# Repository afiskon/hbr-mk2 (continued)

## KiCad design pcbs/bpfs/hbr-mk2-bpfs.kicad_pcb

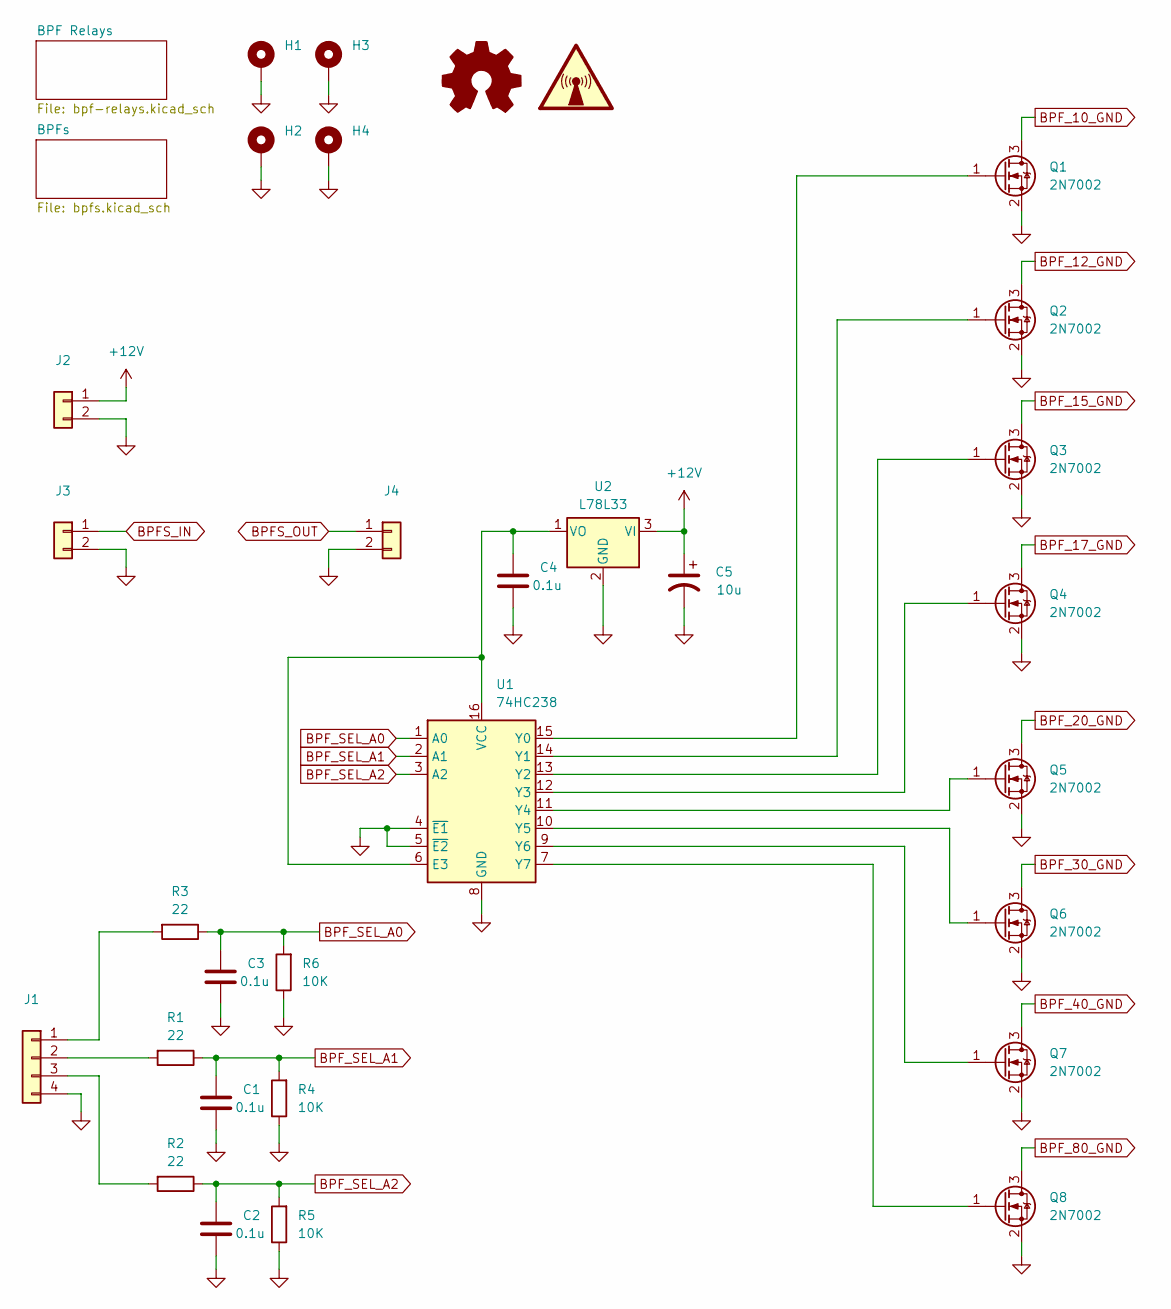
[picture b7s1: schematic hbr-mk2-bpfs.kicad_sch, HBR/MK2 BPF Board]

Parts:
C1, C2, C3, C4: 0.1u; C_0805_2012Metric_Pad1.18x1.45mm_HandSolder
C5: 10u; CP_Elec_4x5.4
H1, H2, H3, H4: MountingHole_Pad; MountingHole_3.5mm_Pad_Via
J1: Conn_01x04; PinHeader_1x04_P2.54mm_Vertical
J2, J3, J4: Conn_01x02; PinHeader_1x02_P2.54mm_Vertical
Q1, Q2, Q3, Q4, Q5, Q6, Q7, Q8: 2N7002; SOT-23
R1, R2, R3: 22; R_0805_2012Metric_Pad1.20x1.40mm_HandSolder
R4, R5, R6: 10K; R_0805_2012Metric_Pad1.20x1.40mm_HandSolder
SYM1: Logo_Open_Hardware_Small; OSHW-Logo2_9.8x8mm_SilkScreen
SYM2: SYM_Radio_Waves_Large; KiCad-Logo2_5mm_SilkScreen
U1: 74HC238; SO-16_5.3x10.2mm_P1.27mm
U2: L78L33; TO-92_HandSolder

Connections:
+12V: C5.1, J2.1, U2.3 (VI); also elsewhere on the board
BPFS_IN: J3.1; also elsewhere on the board
BPFS_OUT: J4.1; also elsewhere on the board
BPF_10_GND: Q1.3 (D); also elsewhere on the board
BPF_12_GND: Q2.3 (D); also elsewhere on the board
BPF_15_GND: Q3.3 (D); also elsewhere on the board
BPF_17_GND: Q4.3 (D); also elsewhere on the board
BPF_20_GND: Q5.3 (D); also elsewhere on the board
BPF_30_GND: Q6.3 (D); also elsewhere on the board
BPF_40_GND: Q7.3 (D); also elsewhere on the board
BPF_80_GND: Q8.3 (D); also elsewhere on the board
BPF_SEL_A0: C3.2, R3.1, R6.2, U1.1 (A0)
BPF_SEL_A1: C1.2, R1.1, R4.2, U1.2 (A1)
BPF_SEL_A2: C2.2, R2.1, R5.2, U1.3 (A2)
GND: C1.1, C2.1, C3.1, C4.1, C5.2, H1.1, H2.1, H3.1, H4.1, J1.4, J2.2, J3.2, J4.2, Q1.2 (S), Q2.2 (S), Q3.2 (S), Q4.2 (S), Q5.2 (S), Q6.2 (S), Q7.2 (S), Q8.2 (S), R4.1, R5.1, R6.1, U1.4 (~E1), U1.5 (~E2), U1.8 (GND), U2.2 (GND); also elsewhere on the board
unnamed: J1.1, R3.2
unnamed: J1.2, R1.2
unnamed: J1.3, R2.2
unnamed: Q1.1 (G), U1.15 (Y0)
unnamed: Q2.1 (G), U1.14 (Y1)
unnamed: Q3.1 (G), U1.13 (Y2)
unnamed: Q4.1 (G), U1.12 (Y3)
unnamed: Q5.1 (G), U1.11 (Y4)
unnamed: Q6.1 (G), U1.10 (Y5)
unnamed: Q7.1 (G), U1.9 (Y6)
unnamed: Q8.1 (G), U1.7 (Y7)
unnamed: C4.2, U1.6 (E3), U1.16 (VCC), U2.1 (VO)

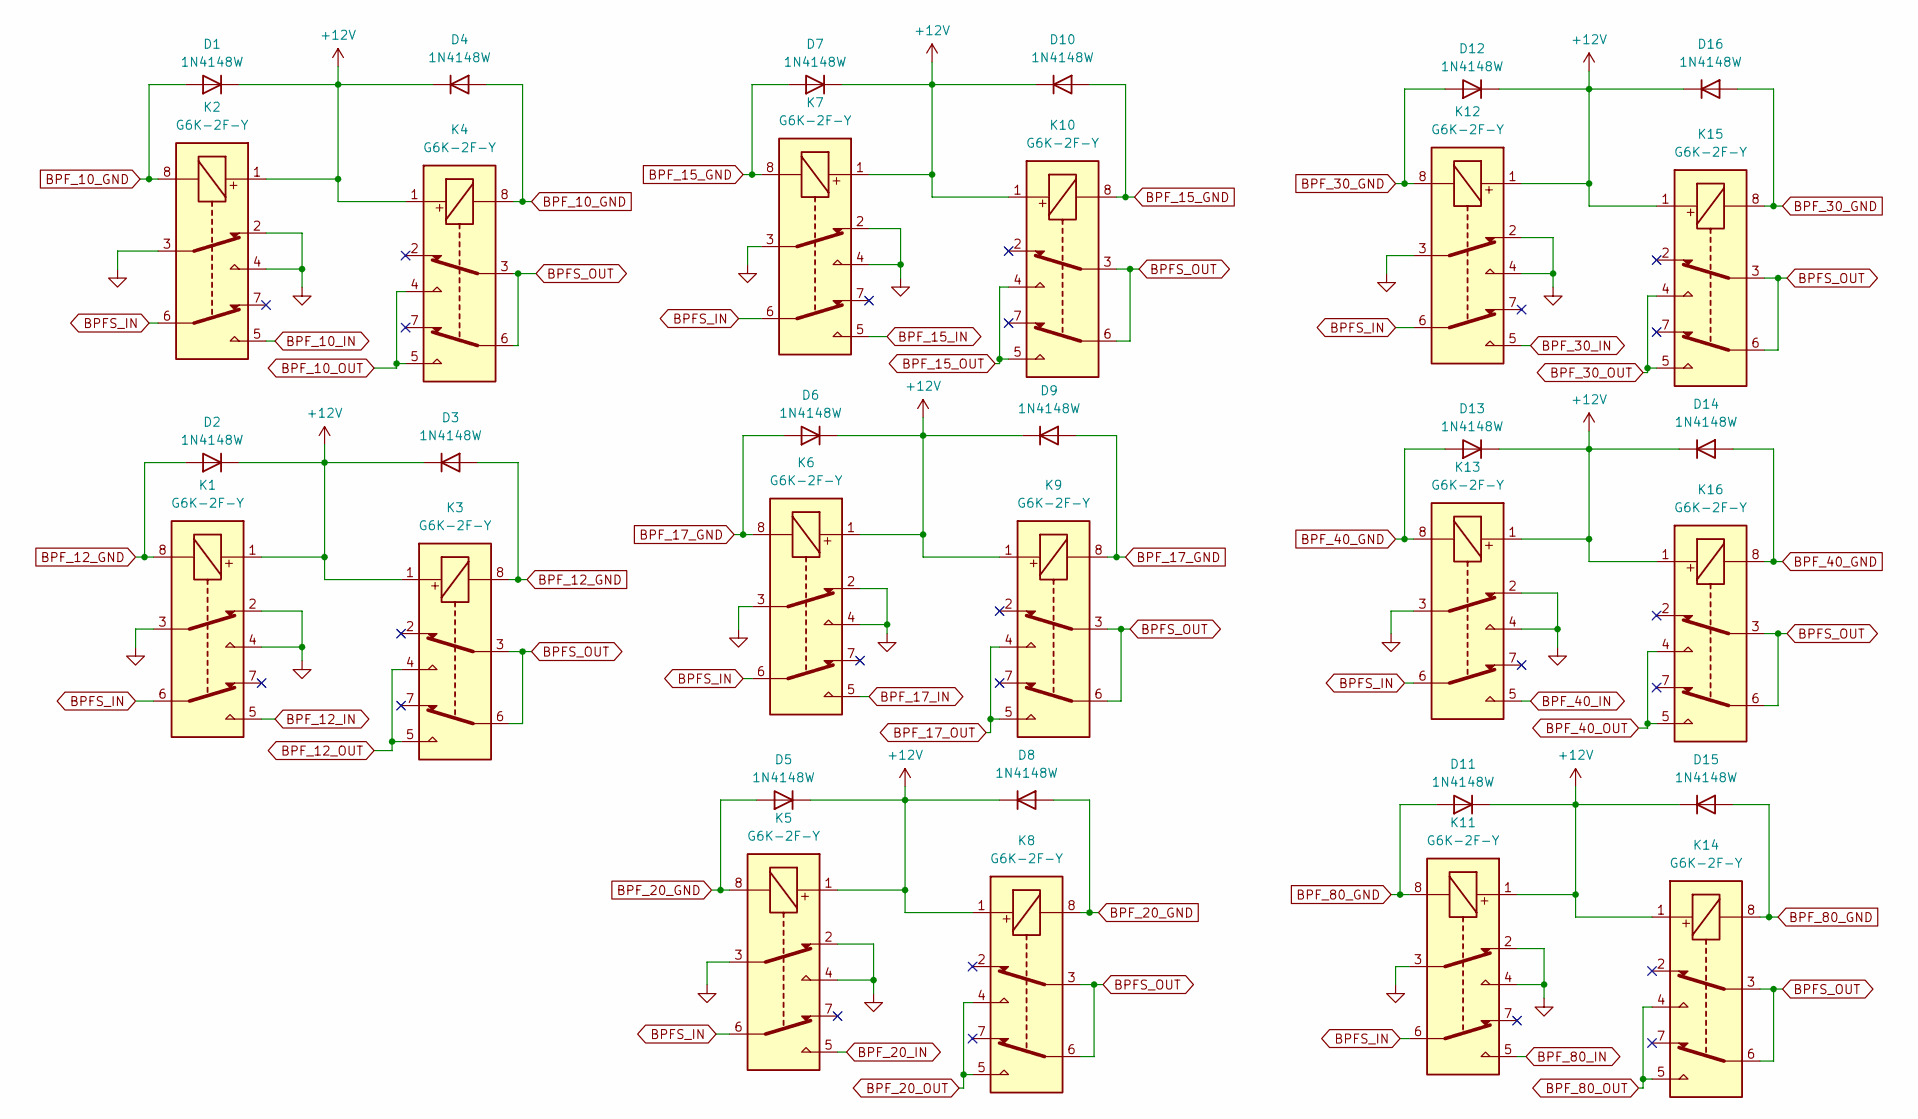
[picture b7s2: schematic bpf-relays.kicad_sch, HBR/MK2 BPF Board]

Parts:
D1, D2, D3, D4, D5, D6, D7, D8, D9, D10, D11, D12, D13, D14, D15, D16: 1N4148W; D_SOD-123
K1, K2, K3, K4, K5, K6, K7, K8, K9, K10, K11, K12, K13, K14, K15, K16: G6K-2F-Y; Relay_DPDT_Omron_G6K-2F-Y

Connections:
+12V: D1.1 (K), D2.1 (K), D3.1 (K), D4.1 (K), D5.1 (K), D6.1 (K), D7.1 (K), D8.1 (K), D9.1 (K), D10.1 (K), D11.1 (K), D12.1 (K), D13.1 (K), D14.1 (K), D15.1 (K), D16.1 (K), K1.1, K2.1, K3.1, K4.1, K5.1, K6.1, K7.1, K8.1, K9.1, K10.1, K11.1, K12.1, K13.1, K14.1, K15.1, K16.1; also elsewhere on the board
BPFS_IN: K1.6, K2.6, K5.6, K6.6, K7.6, K11.6, K12.6, K13.6; also elsewhere on the board
BPFS_OUT: K3.3, K3.6, K4.3, K4.6, K8.3, K8.6, K9.3, K9.6, K10.3, K10.6, K14.3, K14.6, K15.3, K15.6, K16.3, K16.6; also elsewhere on the board
BPF_10_GND: D1.2 (A), D4.2 (A), K2.8, K4.8; also elsewhere on the board
BPF_10_IN: K2.5; also elsewhere on the board
BPF_10_OUT: K4.4, K4.5; also elsewhere on the board
BPF_12_GND: D2.2 (A), D3.2 (A), K1.8, K3.8; also elsewhere on the board
BPF_12_IN: K1.5; also elsewhere on the board
BPF_12_OUT: K3.4, K3.5; also elsewhere on the board
BPF_15_GND: D7.2 (A), D10.2 (A), K7.8, K10.8; also elsewhere on the board
BPF_15_IN: K7.5; also elsewhere on the board
BPF_15_OUT: K10.4, K10.5; also elsewhere on the board
BPF_17_GND: D6.2 (A), D9.2 (A), K6.8, K9.8; also elsewhere on the board
BPF_17_IN: K6.5; also elsewhere on the board
BPF_17_OUT: K9.4, K9.5; also elsewhere on the board
BPF_20_GND: D5.2 (A), D8.2 (A), K5.8, K8.8; also elsewhere on the board
BPF_20_IN: K5.5; also elsewhere on the board
BPF_20_OUT: K8.4, K8.5; also elsewhere on the board
BPF_30_GND: D12.2 (A), D16.2 (A), K12.8, K15.8; also elsewhere on the board
BPF_30_IN: K12.5; also elsewhere on the board
BPF_30_OUT: K15.4, K15.5; also elsewhere on the board
BPF_40_GND: D13.2 (A), D14.2 (A), K13.8, K16.8; also elsewhere on the board
BPF_40_IN: K13.5; also elsewhere on the board
BPF_40_OUT: K16.4, K16.5; also elsewhere on the board
BPF_80_GND: D11.2 (A), D15.2 (A), K11.8, K14.8; also elsewhere on the board
BPF_80_IN: K11.5; also elsewhere on the board
BPF_80_OUT: K14.4, K14.5; also elsewhere on the board
GND: K1.2, K1.3, K1.4, K2.2, K2.3, K2.4, K5.2, K5.3, K5.4, K6.2, K6.3, K6.4, K7.2, K7.3, K7.4, K11.2, K11.3, K11.4, K12.2, K12.3, K12.4, K13.2, K13.3, K13.4; also elsewhere on the board

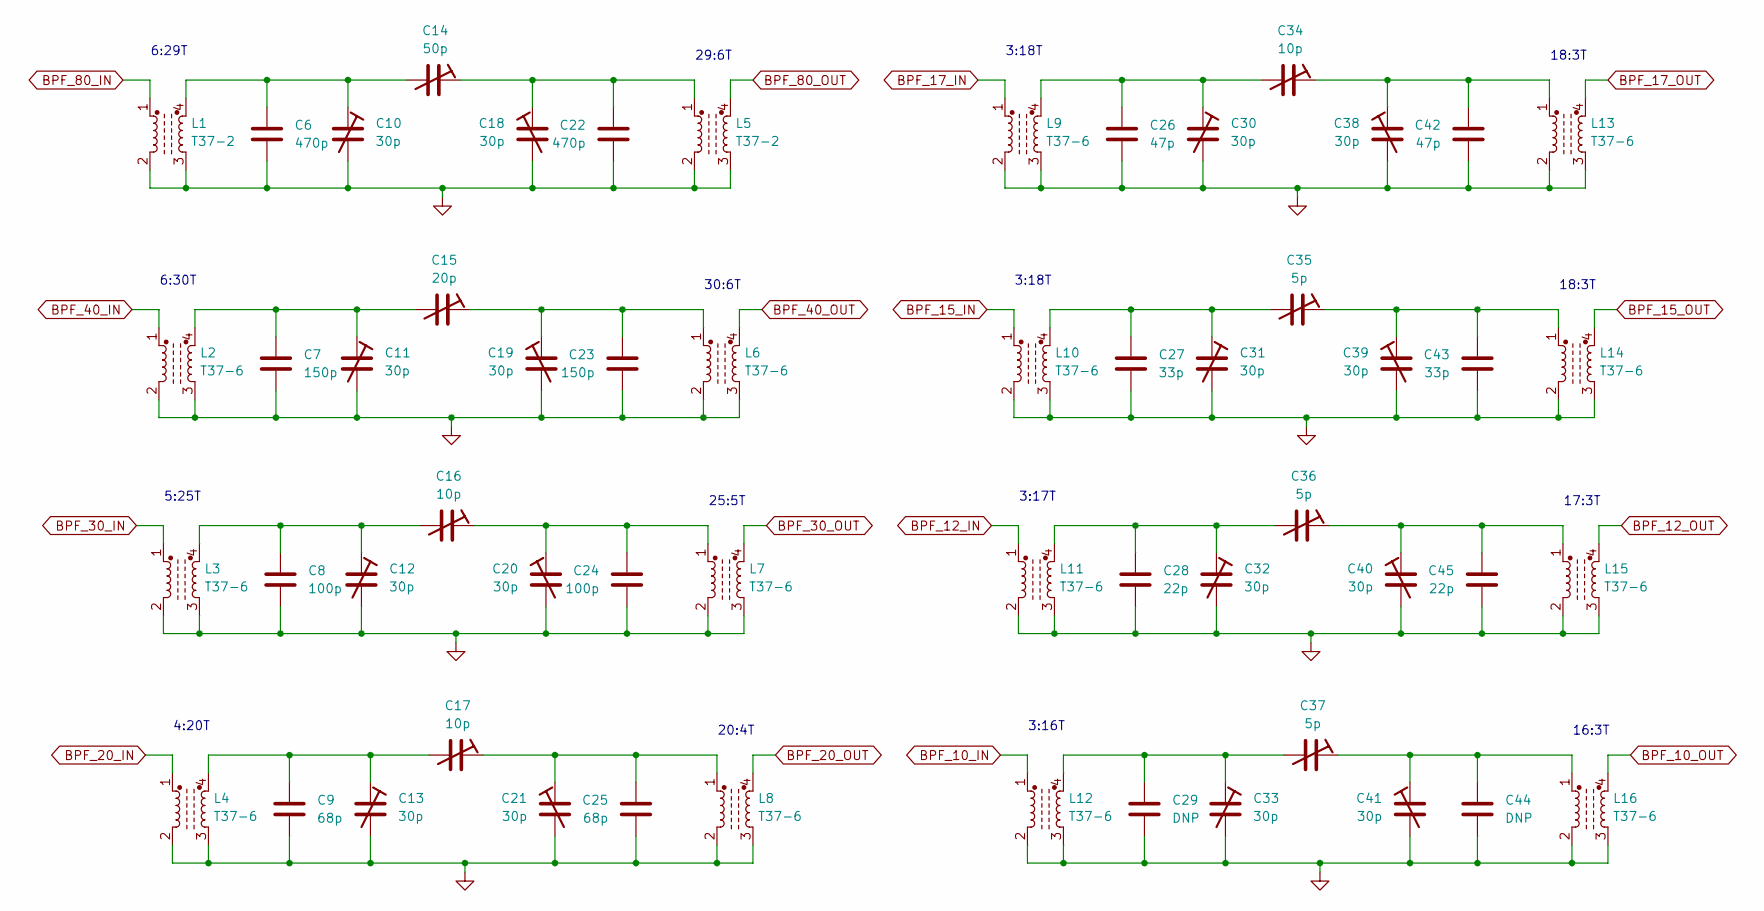
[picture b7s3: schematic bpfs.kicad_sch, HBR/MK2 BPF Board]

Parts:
C6, C22: 470p; C_0805_2012Metric_Pad1.18x1.45mm_HandSolder
C7, C23: 150p; C_0805_2012Metric_Pad1.18x1.45mm_HandSolder
C8, C24: 100p; C_0805_2012Metric_Pad1.18x1.45mm_HandSolder
C9, C25: 68p; C_0805_2012Metric_Pad1.18x1.45mm_HandSolder
C10, C11, C12, C13, C18, C19, C20, C21, C30, C31, C32, C33, C38, C39, C40, C41: 30p; C_Trim_THD_L7.0mm_W6.5mm_P5.00mm
C14: 50p; C_Trim_THD_L7.0mm_W6.5mm_P5.00mm
C15: 20p; C_Trim_THD_L7.0mm_W6.5mm_P5.00mm
C16, C17, C34: 10p; C_Trim_THD_L7.0mm_W6.5mm_P5.00mm
C26, C42: 47p; C_0805_2012Metric_Pad1.18x1.45mm_HandSolder
C27, C43: 33p; C_0805_2012Metric_Pad1.18x1.45mm_HandSolder
C28, C45: 22p; C_0805_2012Metric_Pad1.18x1.45mm_HandSolder
C29, C44: DNP; C_0805_2012Metric_Pad1.18x1.45mm_HandSolder
C35, C36, C37: 5p; C_Trim_THD_L7.0mm_W6.5mm_P5.00mm
L1, L5: T37-2; DIP-4_W7.62mm
L2, L3, L4, L6, L7, L8, L9, L10, L11, L12, L13, L14, L15, L16: T37-6; DIP-4_W7.62mm

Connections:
BPF_10_IN: L12.1; also elsewhere on the board
BPF_10_OUT: L16.4; also elsewhere on the board
BPF_12_IN: L11.1; also elsewhere on the board
BPF_12_OUT: L15.4; also elsewhere on the board
BPF_15_IN: L10.1; also elsewhere on the board
BPF_15_OUT: L14.4; also elsewhere on the board
BPF_17_IN: L9.1; also elsewhere on the board
BPF_17_OUT: L13.4; also elsewhere on the board
BPF_20_IN: L4.1; also elsewhere on the board
BPF_20_OUT: L8.4; also elsewhere on the board
BPF_30_IN: L3.1; also elsewhere on the board
BPF_30_OUT: L7.4; also elsewhere on the board
BPF_40_IN: L2.1; also elsewhere on the board
BPF_40_OUT: L6.4; also elsewhere on the board
BPF_80_IN: L1.1; also elsewhere on the board
BPF_80_OUT: L5.4; also elsewhere on the board
GND: C6.2, C7.2, C8.2, C9.2, C10.2, C11.2, C12.2, C13.2, C18.2, C19.2, C20.2, C21.2, C22.2, C23.2, C24.2, C25.2, C26.2, C27.2, C28.2, C29.2, C30.2, C31.2, C32.2, C33.2, C38.2, C39.2, C40.2, C41.2, C42.2, C43.2, C44.2, C45.2, L1.2, L1.3, L2.2, L2.3, L3.2, L3.3, L4.2, L4.3, L5.2, L5.3, L6.2, L6.3, L7.2, L7.3, L8.2, L8.3, L9.2, L9.3, L10.2, L10.3, L11.2, L11.3, L12.2, L12.3, L13.2, L13.3, L14.2, L14.3, L15.2, L15.3, L16.2, L16.3; also elsewhere on the board
unnamed: C6.1, C10.1, C14.2, L1.4
unnamed: C7.1, C11.1, C15.2, L2.4
unnamed: C8.1, C12.1, C16.2, L3.4
unnamed: C9.1, C13.1, C17.2, L4.4
unnamed: C14.1, C18.1, C22.1, L5.1
unnamed: C15.1, C19.1, C23.1, L6.1
unnamed: C16.1, C20.1, C24.1, L7.1
unnamed: C17.1, C21.1, C25.1, L8.1
unnamed: C26.1, C30.1, C34.2, L9.4
unnamed: C27.1, C31.1, C35.2, L10.4
unnamed: C28.1, C32.1, C36.2, L11.4
unnamed: C29.1, C33.1, C37.2, L12.4
unnamed: C34.1, C38.1, C42.1, L13.1
unnamed: C35.1, C39.1, C43.1, L14.1
unnamed: C36.1, C40.1, C45.1, L15.1
unnamed: C37.1, C41.1, C44.1, L16.1

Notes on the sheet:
18:3T
3:18T
6:29T
5:25T
3:16T
4:20T
29:6T
16:3T
20:4T
6:30T
30:6T
17:3T
3:17T
25:5T

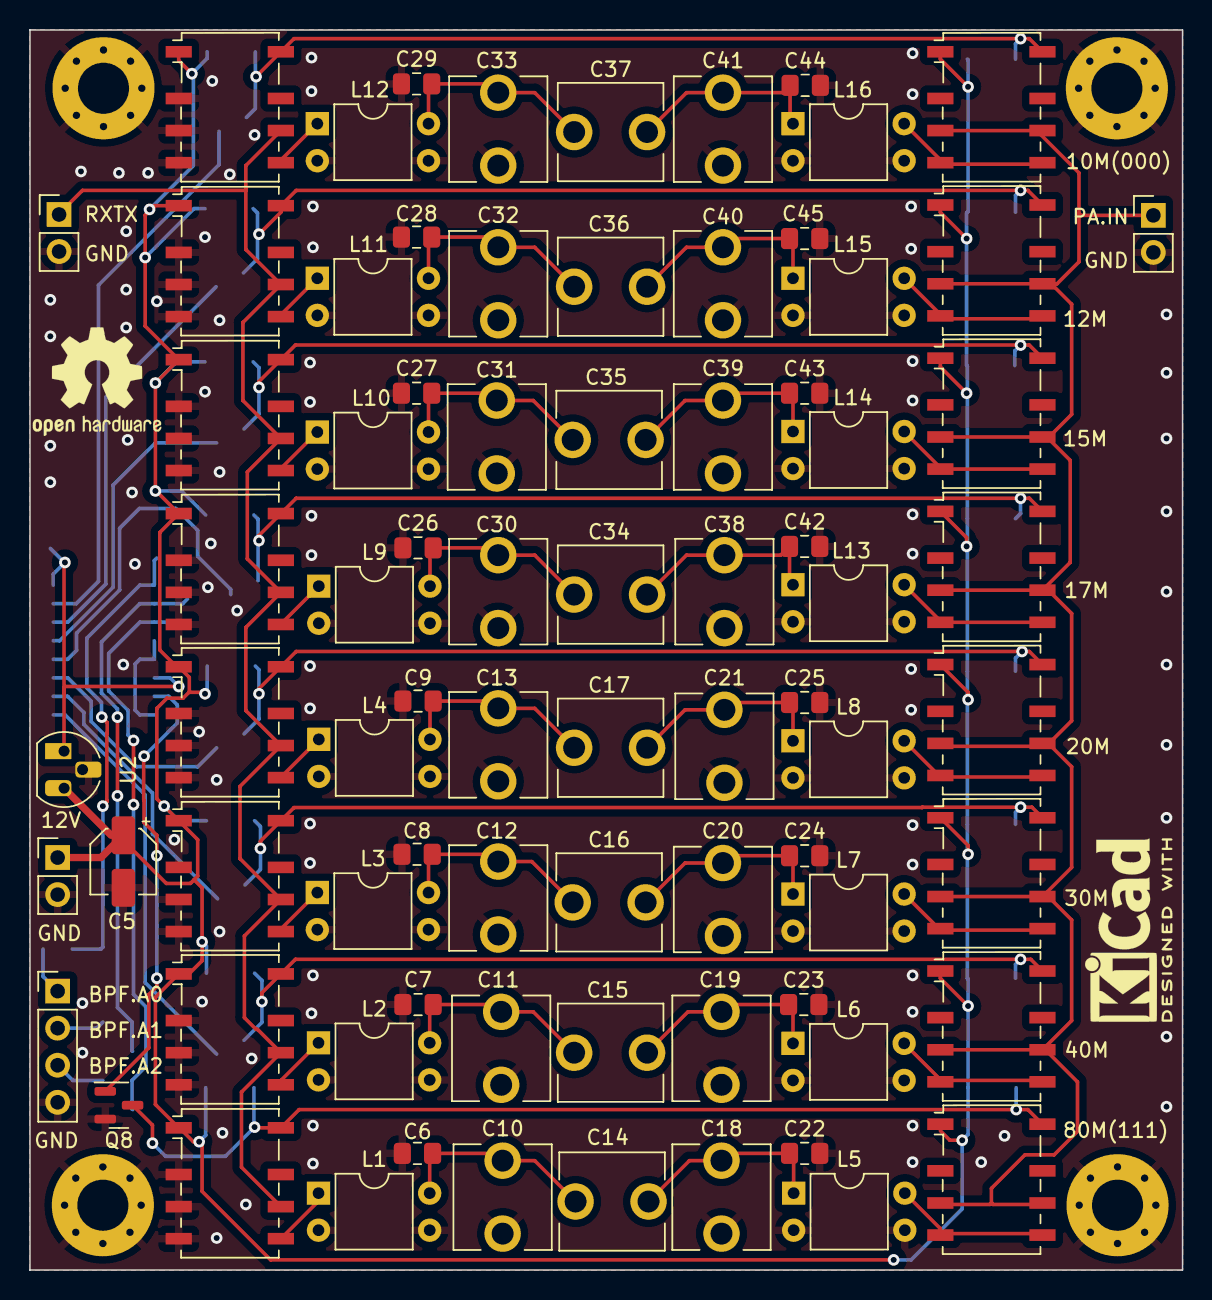
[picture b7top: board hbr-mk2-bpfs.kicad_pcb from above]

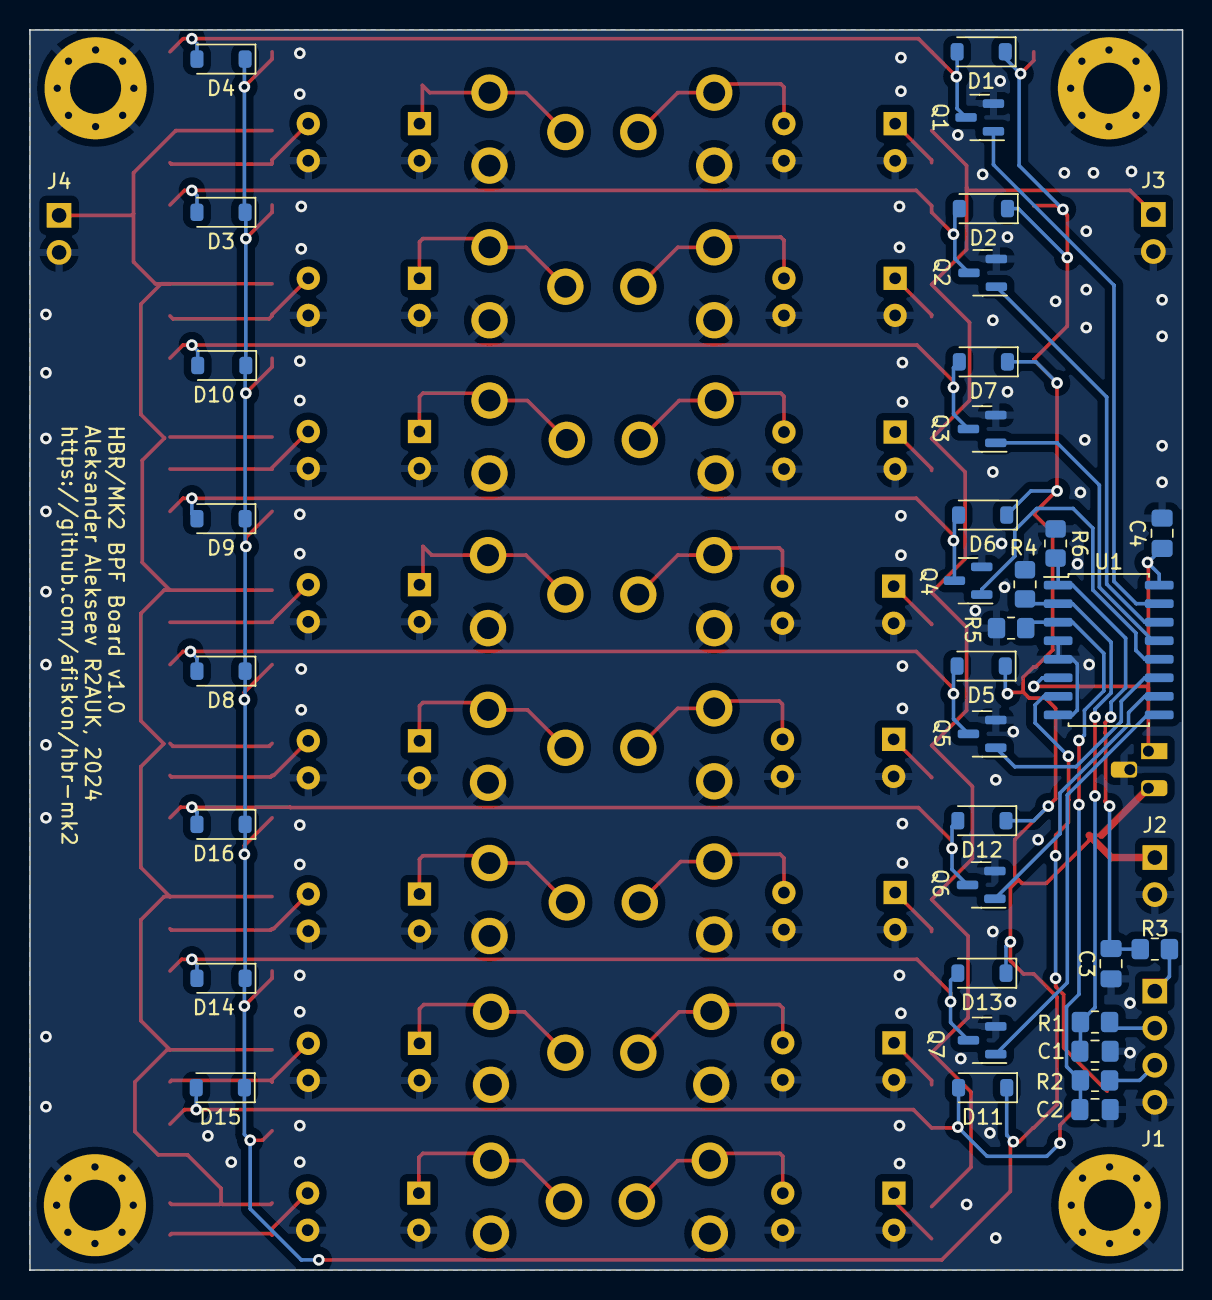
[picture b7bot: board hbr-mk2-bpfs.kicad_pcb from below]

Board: 2 copper layers, 79.0 x 85.0 mm, 119 parts (34 on the bottom side), 59 nets.

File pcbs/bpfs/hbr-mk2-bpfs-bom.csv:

Reference(s),Qty,Value,Footprint
"C1, C2, C3, C4",4,0.1u,Capacitor_SMD:C_0805_2012Metric_Pad1.18x1.45mm_HandSolder
C5,1,10u,Capacitor_SMD:CP_Elec_4x5.4
"C6, C22",2,470p,Capacitor_SMD:C_0805_2012Metric_Pad1.18x1.45mm_HandSolder
"C7, C23",2,150p,Capacitor_SMD:C_0805_2012Metric_Pad1.18x1.45mm_HandSolder
"C8, C24",2,100p,Capacitor_SMD:C_0805_2012Metric_Pad1.18x1.45mm_HandSolder
"C9, C25",2,68p,Capacitor_SMD:C_0805_2012Metric_Pad1.18x1.45mm_HandSolder
"C10, C11, C12, C13, C18, C19, C20, C21, C30, C31, C32, C33, C38, C39, C40, C41",16,30p,My_Library:C_Trim_THD_L7.0mm_W6.5mm_P5.00mm
C14,1,50p,My_Library:C_Trim_THD_L7.0mm_W6.5mm_P5.00mm
C15,1,20p,My_Library:C_Trim_THD_L7.0mm_W6.5mm_P5.00mm
"C16, C17, C34",3,10p,My_Library:C_Trim_THD_L7.0mm_W6.5mm_P5.00mm
"C26, C42",2,47p,Capacitor_SMD:C_0805_2012Metric_Pad1.18x1.45mm_HandSolder
"C27, C43",2,33p,Capacitor_SMD:C_0805_2012Metric_Pad1.18x1.45mm_HandSolder
"C28, C45",2,22p,Capacitor_SMD:C_0805_2012Metric_Pad1.18x1.45mm_HandSolder
"C35, C36, C37",3,5p,My_Library:C_Trim_THD_L7.0mm_W6.5mm_P5.00mm
"D1, D2, D3, D4, D5, D6, D7, D8, D9, D10, D11, D12, D13, D14, D15, D16",16,1N4148W,Diode_SMD:D_SOD-123
"K1, K2, K3, K4, K5, K6, K7, K8, K9, K10, K11, K12, K13, K14, K15, K16",16,G6K-2F-Y,Relay_SMD:Relay_DPDT_Omron_G6K-2F-Y
"L1, L5",2,T37-2,Package_DIP:DIP-4_W7.62mm
"L2, L3, L4, L6, L7, L8, L9, L10, L11, L12, L13, L14, L15, L16",14,T37-6,Package_DIP:DIP-4_W7.62mm
"Q1, Q2, Q3, Q4, Q5, Q6, Q7, Q8",8,2N7002,Package_TO_SOT_SMD:SOT-23
"R1, R2, R3",3,22,Resistor_SMD:R_0805_2012Metric_Pad1.20x1.40mm_HandSolder
"R4, R5, R6",3,10K,Resistor_SMD:R_0805_2012Metric_Pad1.20x1.40mm_HandSolder
U1,1,74HC238,Package_SO:SO-16_5.3x10.2mm_P1.27mm
U2,1,L78L33,Package_TO_SOT_THT:TO-92_HandSolder

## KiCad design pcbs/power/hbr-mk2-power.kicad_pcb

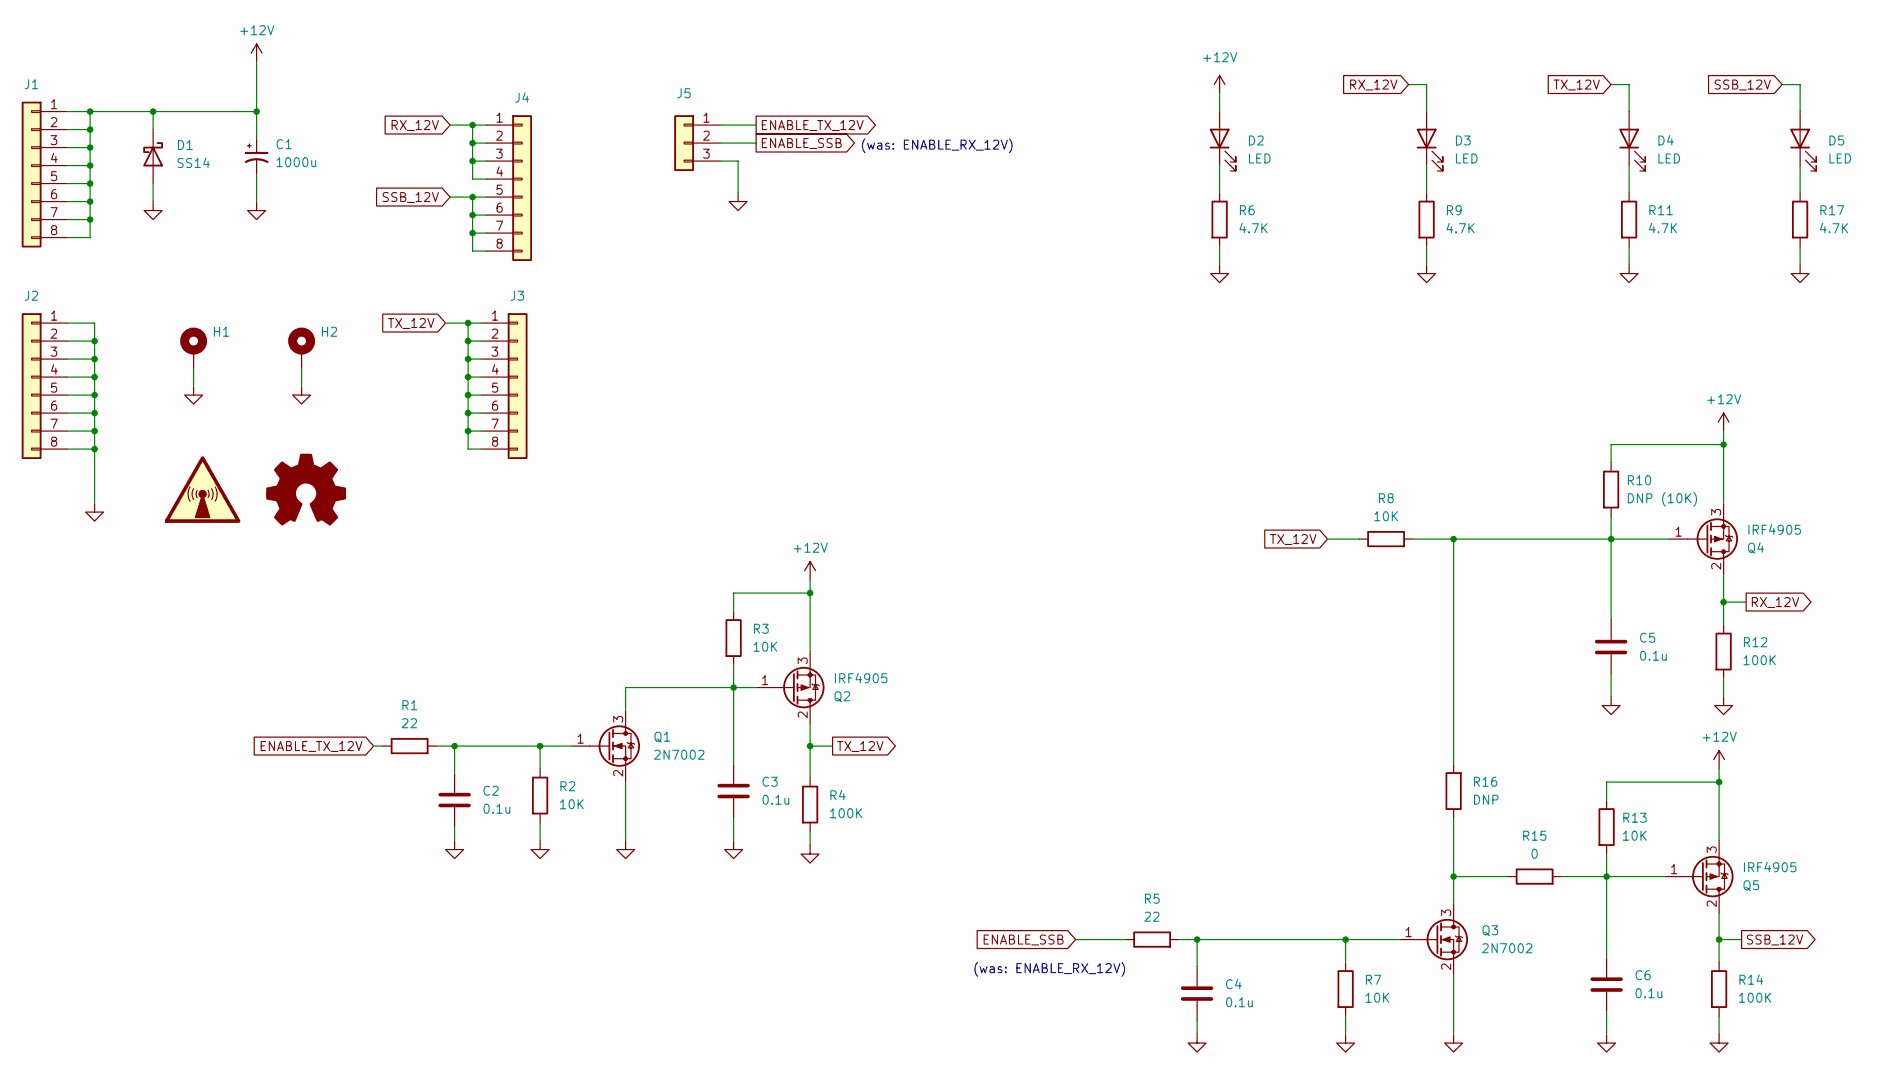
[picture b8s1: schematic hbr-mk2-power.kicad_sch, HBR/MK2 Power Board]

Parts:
C1: 1000u; CP_Radial_D13.0mm_P5.00mm
C2, C3, C4, C5, C6: 0.1u; C_0805_2012Metric_Pad1.18x1.45mm_HandSolder
D1: SS14; D_SMA_Handsoldering
D2, D3, D4, D5: LED; LED_0805_2012Metric_Pad1.15x1.40mm_HandSolder
H1, H2: MountingHole_Pad; MountingHole_3.5mm_Pad_Via
J1, J2, J3, J4: Conn_01x08; PinHeader_1x08_P2.54mm_Vertical
J5: Conn_01x03; PinSocket_1x03_P2.54mm_Vertical
Q1, Q3: 2N7002; SOT-23
Q2, Q4, Q5: IRF4905; TO-220-3_Vertical
R1, R5: 22; R_0805_2012Metric_Pad1.20x1.40mm_HandSolder
R2, R3, R7, R8, R13: 10K; R_0805_2012Metric_Pad1.20x1.40mm_HandSolder
R4, R12, R14: 100K; R_0805_2012Metric_Pad1.20x1.40mm_HandSolder
R6, R9, R11, R17: 4.7K; R_0805_2012Metric_Pad1.20x1.40mm_HandSolder
R10: DNP (10K); R_0805_2012Metric_Pad1.20x1.40mm_HandSolder
R15: 0; R_0805_2012Metric_Pad1.20x1.40mm_HandSolder
R16: DNP; R_0805_2012Metric_Pad1.20x1.40mm_HandSolder
SYM1: SYM_Radio_Waves_Large; KiCad-Logo2_5mm_SilkScreen
SYM2: Logo_Open_Hardware_Small; OSHW-Logo2_9.8x8mm_SilkScreen

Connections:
+12V: C1.1, D1.1 (K), D2.2 (A), J1.1, J1.2, J1.3, J1.4, J1.5, J1.6, J1.7, J1.8, Q2.3 (S), Q4.3 (S), Q5.3 (S), R3.1, R10.1, R13.1
ENABLE_SSB: J5.2, R5.1
ENABLE_TX_12V: J5.1, R1.1
GND: C1.2, C2.2, C3.2, C4.2, C5.2, C6.2, D1.2 (A), H1.1, H2.1, J2.1, J2.2, J2.3, J2.4, J2.5, J2.6, J2.7, J2.8, J5.3, Q1.2 (S), Q3.2 (S), R2.2, R4.2, R6.2, R7.2, R9.2, R11.2, R12.2, R14.2, R17.2
unnamed: D2.1 (K), R6.1
unnamed: D3.1 (K), R9.1
unnamed: D4.1 (K), R11.1
unnamed: D5.1 (K), R17.1
unnamed: C3.1, Q1.3 (D), Q2.1 (G), R3.2
unnamed: C2.1, Q1.1 (G), R1.2, R2.1
unnamed: Q3.3 (D), R15.1, R16.1
unnamed: C4.1, Q3.1 (G), R5.2, R7.1
unnamed: C5.1, Q4.1 (G), R8.2, R10.2, R16.2
unnamed: C6.1, Q5.1 (G), R13.2, R15.2
RX_12V: D3.2 (A), J4.1, J4.2, J4.3, J4.4, Q4.2 (D), R12.1
SSB_12V: D5.2 (A), J4.5, J4.6, J4.7, J4.8, Q5.2 (D), R14.1
TX_12V: D4.2 (A), J3.1, J3.2, J3.3, J3.4, J3.5, J3.6, J3.7, J3.8, Q2.2 (D), R4.1, R8.1

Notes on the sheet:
(was: ENABLE_RX_12V)

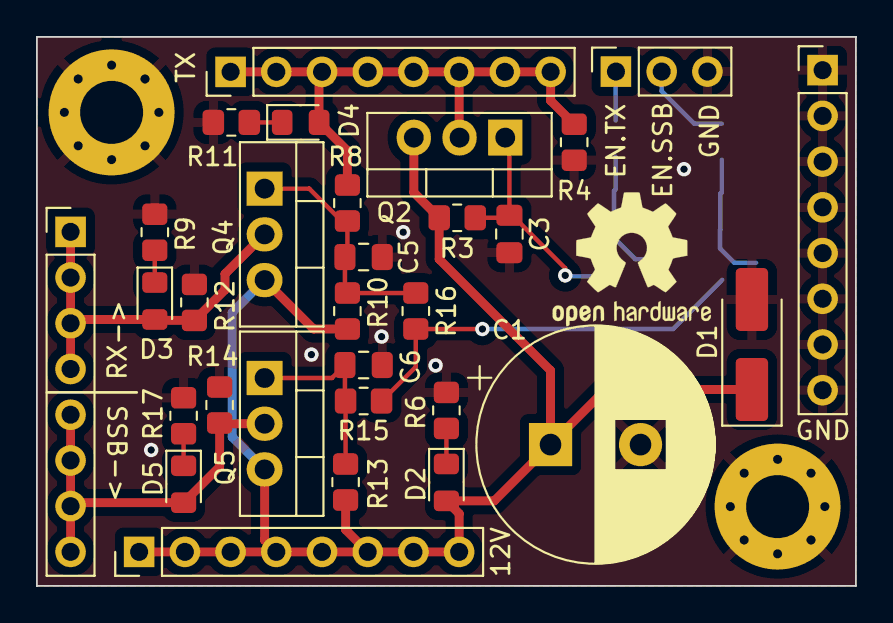
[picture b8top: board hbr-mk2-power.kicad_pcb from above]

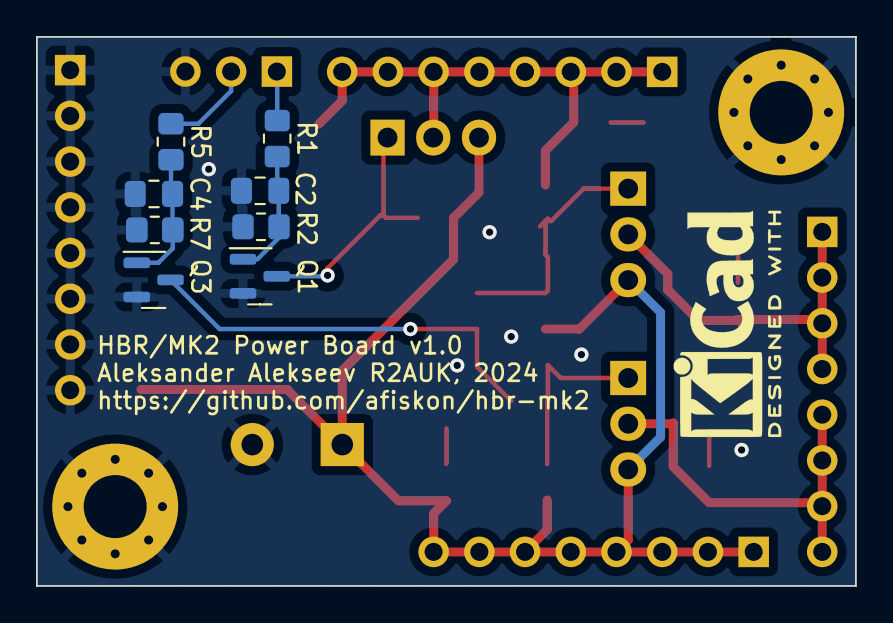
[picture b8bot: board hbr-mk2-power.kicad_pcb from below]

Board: 2 copper layers, 45.5 x 30.5 mm, 42 parts (9 on the bottom side), 17 nets.

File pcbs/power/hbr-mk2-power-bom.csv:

Reference(s),Qty,Value,Footprint
C1,1,1000u,Capacitor_THT:CP_Radial_D13.0mm_P5.00mm
"C3, C4, C5, C6",4,0.1u,Capacitor_SMD:C_0805_2012Metric_Pad1.18x1.45mm_HandSolder
D1,1,SS14,Diode_SMD:D_SMA_Handsoldering
"D2, D3, D4, D5",4,LED,LED_SMD:LED_0805_2012Metric_Pad1.15x1.40mm_HandSolder
"Q1, Q3",2,2N7002,Package_TO_SOT_SMD:SOT-23
"Q2, Q4, Q5",3,IRF4905,Package_TO_SOT_THT:TO-220-3_Vertical
"R1, R5",2,22,Resistor_SMD:R_0805_2012Metric_Pad1.20x1.40mm_HandSolder
"R2, R3, R7, R8, R13",5,10K,Resistor_SMD:R_0805_2012Metric_Pad1.20x1.40mm_HandSolder
"R4, R12, R14",3,100K,Resistor_SMD:R_0805_2012Metric_Pad1.20x1.40mm_HandSolder
"R6, R9, R11, R17",4,4.7K,Resistor_SMD:R_0805_2012Metric_Pad1.20x1.40mm_HandSolder
R15,1,0,Resistor_SMD:R_0805_2012Metric_Pad1.20x1.40mm_HandSolder

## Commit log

2023-12-09 Add OpenSCAD & STL enclosure files
2023-12-09 Add firmware source code
2023-12-09 Add KiCAD project
2023-12-09 Add images/bpfs
2023-12-11 Correct VFO frequencies + fix typo
2023-12-11 Calibrate the S-meter
2023-12-11 Schematic: add S-meter
2023-12-11 Fix typo
2023-12-15 Add CW tone generator + other changes
2023-12-15 Minor changes
2023-12-15 Make CW tone frequency adjustable
2023-12-15 Power S-meter from 8V
2023-12-18 Rename ENABLE_CW_TX to ENABLE_TX
2023-12-18 Rename ENABLE_TX to ENABLE_KEYED_VCC
2023-12-18 Add ENABLE_KEYED_VCC manipulation to keyUp() and keyDown()
2023-12-18 Refactor loopKeyer()
2023-12-18 Rename checkIfModeHasChanged() to checkIfRxModeHasChanged()
2023-12-18 Stop transmitting when user switches the mode
2023-12-18 Refactor changeFrequency(), support transmitting SSB
2023-12-18 Use proper VFO frequency when transmitting CW
2023-12-18 Checking if mode has changed while transmitting is not very useful in practice, so revert this
2023-12-18 Add /TX Common/ schematic sheet
2023-12-18 Schematic: minor changes
2023-12-18 Use 4 dB attenuator for CLK_CW instead of 3 dB one + minor changes
2023-12-18 Use 6 dB attenuator for CLK_CW
2023-12-18 Correct .txDriveStrength values
2023-12-20 Decrease VFO drive strength to ~2 dBm
2023-12-20 Decrease txDriveStrength for 80-20m
2023-12-20 Further tweak VFODriveStrength and txDriveStrength
2023-12-21 Update schematic + minor changes
2023-12-21 Update schematic
2023-12-21 Use target frequency for CH_CW (i.e. no VFO)
2023-12-21 Fix keyUp() implementation
2023-12-21 Add 1.3K resistor before the volume control pot
2023-12-23 Recalibrate S-meter for ADE-6 mixers
2023-12-23 Connect relay contact groups in parallel where appropriate
2023-12-23 Add PA schematic + some minor changes
2023-12-23 Schematic: minor fixes
2023-12-23 Add diodes for BPF relays
2023-12-24 Schematic: add low pass filters
2023-12-24 Schematic: add relays to /LPFs/ sheet
2023-12-25 Schematic: simplify 80M LPF
2023-12-26 Schematic: correct number of turns for LPF inductors
2023-12-27 Firmware: correct LPF switching
2023-12-28 Add lpfs/*.png, power/cw/*.png
2023-12-30 Correct formatting
2023-12-30 Firmware: use lower clock speed to reduce digital noise
2023-12-30 Use standard I2C speed + tweak LOOP_DELAY
2023-12-30 Firmware: further reduce clock speed
2023-12-30 Revert "Firmware: further reduce clock speed"
    This reverts commit 10d4aec0e390a78ca015cad832a2514f9e4502a8.
2023-12-30 Schematic: add a bit more 0.1u capacitors
2024-01-02 updateSWRMeter(): minor changes
2024-01-02 Firmware: correct updateSWRMeter()
2024-01-02 Schematic: add SWR bridge
2024-01-03 Firmware: minor chanes
2024-01-03 Firmware: transmit saved message when pressing XMIT
2024-01-03 Firmware: refactor comments a bit
2024-01-03 Update enclosure
2024-01-08 Tweak updateSWRMeter() a little
2024-01-10 Add /TX SSB/ sheet
2024-01-22 Remove /CW TX/ sheet
2024-01-30 Move PCB KiCad projects and gerber files from a sandbox repository
2024-04-24 Update firmware according to the recent PCB changes
2024-04-25 Digital board: correct the silkscreen
2024-04-25 AF PCB: fix typo
2024-04-26 Mark C3,C4,C7,C8 as DNP
2024-04-26 Bump Digital PCB revision
2024-04-30 Update firmware according to the recent changes in the schematic
2024-04-30 Add a little hint to RXTX PCB schematic
2024-04-30 Allow using NEXT/PREV buttons in FAST mode
2024-05-03 No delay is needed when releasing PTT
2024-05-03 Add block diagram
2024-05-05 Update images/bpfs
2024-05-06 LPFs: update R11,R12 values
2024-05-06 Update images/power/cw/*
2024-05-06 Add images/power/ssb/*
2024-05-06 Rename images/power/ssb/*.png files
2024-05-06 Add .DS_Store to gitignore
2024-05-12 Add images/enclosure/*.jpg
2024-05-18 Add a link to the discussion on AmateurRadioBuilders@groups.io
2024-05-19 Firmware upgrade
2024-05-19 Remove the outdated images. I will update the article accordingly
2024-05-20 Various minor improvements
2024-05-20 Update PDFs according to the recent changes
2024-05-21 Remove empty line
2024-05-23 Add a few comments about the compression to the schematic
2024-05-23 Improve si5351_Calc() accuracy
2024-05-24 Add a warning about crappy ADE-1-24 mixers
2024-05-24 bomgen.pl: add MC33078 as a possible replacement for NE5532
2024-05-24 Update LICENSE year
2024-05-24 Add missing semicolon
2024-05-26 Fix page 15 of the schematic
2024-07-31 Add link to the article on dxzone
2024-08-02 Convert to platformio
2024-08-08 Transmit saved message on 17 WPM in straight key mode
2026-01-26 Add firmware/build/main.{bin,hex}
